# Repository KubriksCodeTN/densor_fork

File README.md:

# Densor

## About the project

Densor is an intraoral sensor platform, attached to regular dental retainers or aligners, that can take measurements inside the mouth. 

## Rationale

At present, in mouth measurements are typically made with external tools and in a controlled labaratory setting. Thus, real data from users daily lives is missing. To overcome this, we propose using widely used deltal retainers (or aligners), and enhance them with the Densor sensing platform. This way data is collected from inside the mouth without external tools. 

## Features

1. **Contactless transmission:** Densor is completely sealed and interacts with a smartphone via [NFC protocol](https://en.wikipedia.org/wiki/Near-field_communication). 
2. **Energy harvesting:** To stay powered Densor harvests energy, either from the [NFC communication itself](https://github.com/TUDSSL/densor/tree/master/NFC_harvester_battery_free) or from the [temperature gradient between the body and cold water](https://github.com/TUDSSL/densor/tree/master/TEG_harvester_battery_free). 
4. **Free of external hardware:** Operating Densor does not require any specialized tools, other than a NFC-compatible smartphone.

## Project layout

This repository contains the design (both hardware and software) of two versions of Densor, based on the source of energy harvesting. Each version of the project is contained in its own folder:

1. **[Densor with NFC-based energy harvesting from a smartphone](https://github.com/TUDSSL/densor/tree/master/NFC_harvester_battery_free)**, as presented in [this research article](https://dl.acm.org/doi/10.1145/3699746);
2. **[Densor with thermoelectric energy harvesting from drinking cold water](https://github.com/TUDSSL/densor/tree/master/TEG_harvester_battery_free)**.

## Copyright

Copyright (C) 2024 TU Delft Embedded Systems Group/[Sustainable Systems Laboratory](https://github.com/TUDSSL).

MIT License or otherwise specified. See [license](https://github.com/TUDSSL/densor/blob/master/LICENSE.txt) file for details.

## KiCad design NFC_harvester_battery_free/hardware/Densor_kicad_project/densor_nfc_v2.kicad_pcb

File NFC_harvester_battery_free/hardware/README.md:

# Densor - Hardware

## About the project 

This repository contains the design of Densor: an intraoral, actively powered, battery-free platform featuring multi-modal sensors and an extended lifespan. The repository consists of all components that make Densor:
- [Hardware](https://github.com/TUDSSL/densor/tree/master/NFC_harvester_battery_free/hardware)
- [Densor Firmware](https://github.com/TUDSSL/densor/tree/master/NFC_harvester_battery_free/software/DentalSensor_StorageProject)
- [Android app](https://github.com/TUDSSL/densor/tree/master/NFC_harvester_battery_free/software/source_ST25NFCApplication_V3_9)
- [Experiment setup and data collected](https://github.com/TUDSSL/densor/tree/master/NFC_harvester_battery_free/data/experiments)

This folder contains all the harware design files.

## Folder layout

- [Densor Kicad Project](https://github.com/TUDSSL/densor/tree/master/NFC_harvester_battery_free/hardware/Densor_kicad_project) contains the KiCad design files and can be opened with KiCad Version 8.
- [Datasheets](https://github.com/TUDSSL/densor/tree/master/NFC_harvester_battery_free/hardware/datasheets) contains the relavant datasheets of components used.
- [Gerbers Schematic](https://github.com/TUDSSL/densor/tree/master/NFC_harvester_battery_free/hardware/gerbers_schematic) contains the hardware output gerber files and schematic file in _.pdf_ format. This is useful if you wish to build Densor without any changes to the hardware.  

## List of components

| Component                  | Qty | Purchased from                                                                                                                                                                                                            |
|----------------------------|-----|---------------------------------------------------------------------------------------------------------------------------------------------------------------------------------------------------------------------------|
| Storage Capacitor          | 2   | [link to buy](https://www.digikey.com/en/products/detail/seiko-instruments/CPH3225A/8692444)                                                                                                                              |
| Decoupling Capacitor 100nF | 6   | [link to buy](https://nl.farnell.com/en-NL/kemet/c0603x104m4ractu/cap-mlcc-0-1uf-16v-0603/dp/2904941?st=0603%200.1uf)                                                                                                     |
| Zener Diode                | 1   | [link to buy](https://nl.farnell.com/on-semiconductor/mm3z3v6c/zener-diode-0-2w-3-6v-sod-323f/dp/2824925?CMP=i-ddd7-00001003)                                                                                             |
| Schottky Diode             | 1   | [link to buy](https://nl.farnell.com/nexperia/1ps76sb40-115/diode-schottky-sod323/dp/1349646?CMP=i-ddd7-00001003)                                                                                                         |
| Photo Diode                | 1   | [link to buy](https://nl.mouser.com/ProductDetail/Vishay-Semiconductors/VEMD1060X01?qs=pdQl6rENvLQkGyXPnNHd%2FQ%3D%3D&gclid=Cj0KCQjwmvSoBhDOARIsAK6aV7gSam9QYNxRe1G3dFcvfZGu4WvhXWOQdtZbTP3WNCzxGxyePn8TLa0aAiUbEALw_wcB) |
| Debug header               | 1   | [link to buy](https://nl.farnell.com/samtec/ftsh-105-01-l-d-k/connector-header-10pos-2row-1/dp/2856435?CMP=i-ddd7-00001003)                                                                                               |
| FPC connector              | 1   | [link to buy](https://nl.mouser.com/ProductDetail/Molex/503480-0800?qs=bodV9ulq6Gz33SKuZL445g%3D%3D&srsltid=AfmBOoqTYanmI1YXInVOzdpLIJ4tpVXYK3TQdvr3HJ4Y6jSj3ONDx022)                                                     |
| Pin Header 01x04           | 1   | [link to buy](https://nl.mouser.com/ProductDetail/Harwin/M20-9770446?qs=ulE8k0yEMYbCPpMPHeYh4w%3D%3D)                                                                                                                     |
| Resistor 100kohm           | 3   | [link to buy](https://nl.farnell.com/vishay/crcw0603100kfkea/res-100k-1-0-1w-0603-thick-film/dp/1469649?st=0603%20100k)                                                                                                   |
| Resistor 8Mohm             | 1   | [link to buy](https://nl.farnell.com/vishay/crcw06038m06fkea/res-8m06-1-0-1w-0603-thick-film/dp/2138717)                                                                                                                  |
| NFC Tag - ST25DV04K-JFR6D3 | 1   | [link to buy](https://www.digikey.nl/en/products/detail/stmicroelectronics/ST25DV64K-JFR6D3/7312974)                                                                                                                      |
| RTC - AM1805               | 1   | [link to buy](https://nl.farnell.com/en-NL/abracon/ab1805-t3/real-time-clock-i2c-qfn-16/dp/2467703?st=ab1805)                                                                                                             |
| MCU - STM32L021F3Ux        | 1   | [link to buy](https://www.digikey.nl/en/products/detail/stmicroelectronics/STM32L021F4U6TR/6166967)                                                                                                                       |
| Accelerometer - LIS2DW12   | 1   | [link to buy](https://nl.farnell.com/en-NL/stmicroelectronics/lis2dw12tr/lga-12-i-mems-digital-o-p-motion/dp/2849615?st=LIS2DW12TR)                                                                                       |
| SPDT - TS3A44159           | 1   | [link to buy](https://www.digikey.nl/en/products/detail/texas-instruments/TS3A44159RSVR/1909585)                                                                                                                          |
| Temperature sensor - TMP117AIDRVR | 1  | [link to buy](https://www.mouser.it/en/ProductDetail/Texas-Instruments/TMP117AIDRVR?qs=qSfuJ%252Bfl%2Fd6nh9h5HydMXQ%3D%3D) |
| Crystal                    | 1   | [link to buy](https://nl.farnell.com/en-NL/abracon/abs05w-32-768khz-j-2-t/crystal-32-768khz-4pf-smd-1-6/dp/2850126?st=abs05w)                                                                                             |
| Solder paste               | -   | [link to buy](https://www.digikey.nl/en/products/detail/chip-quik-inc/SMD291SNL50T3/5130160)                                                                                                                              |

## Copyright

Copyright (C) 2024 TU Delft Embedded Systems Group/Sustainable Systems Laboratory.

MIT Licence or otherwise specified. See [license](https://github.com/TUDSSL/ENGAGE/blob/master/LICENSE) file for details.

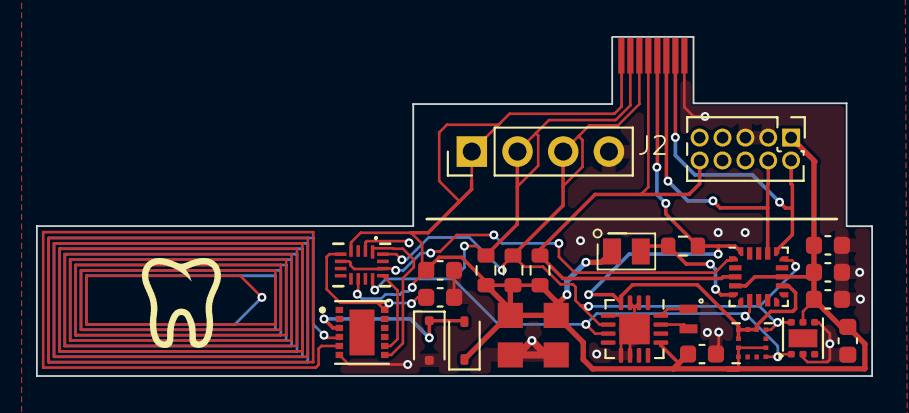
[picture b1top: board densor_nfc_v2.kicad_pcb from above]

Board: 2 copper layers, 46.4 x 18.8 mm, 26 parts (0 on the bottom side), 17 nets.

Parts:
C1, C2: C_Polarized; CPX3225A
C4, C5, C6, C7, C12, C13, C14: 100n; C_0603_1608Metric
D1: D_Zener_3v3; D_SOD-323F
D2: BAS316; D_SOD-323
D3: D_Photo; pd_vemd1060x01
J1: Conn_ARM_JTAG_SWD_10; PinHeader_2x05_P1.27mm_Vertical
J2: Conn_01x08_Pin; fpc_503480-0800
J3: Conn_01x04_Pin; PinHeader_1x04_P2.54mm_Vertical
R2, R3, R4: 100k; R_0603_1608Metric
R7: R; R_0603_1608Metric
U1: ST25DV04K-JFR6D3; PSON50P300X300X60-13N
U2: AM1805; QFN-16-1EP_3x3mm_P0.5mm_EP1.7x1.7mm
U3: TMP117xxDRV; WSON-6-1EP_2x2mm_P0.65mm_EP1x1.6mm
U4: STM32L011F3Ux; ST_UFQFPN-20_3x3mm_P0.5mm
U5: LIS2DW12; Kionix_LGA-12_2x2mm_P0.5mm_LayoutBorder2x4y
U6: TS3A44159; RSV16
Y1: Crystal; ABS05W_Crystal

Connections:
/AC0: U1.4 (AC0), U1.5 (AC1)
/NFC_SWITCH: U4.1 (PC14), U6.6 (IN3-4), U6.14 (IN1-2)
/PSW: J2.5, R7.2, U2.4 (PSW/nIRQ2), U4.12 (VSS), U4.20 (PB9), U5.5 (NC), U5.6 (GND), U5.7 (RES), U5.8 (GND)
/V_EH: D1.1 (K), D2.2 (A), U1.3 (V_EH)
/V_MCU: C1.1, C2.1, C4.1, C5.2, C6.1, C7.2, C12.2, C14.2, D2.1 (K), D3.1 (K), J1.1 (VTref), J2.1, J3.1, R2.1, R3.1, R4.1, U2.13 (VCC), U3.5 (V+), U4.4 (VDDA), U4.13 (VDD), U5.2 (CS), U5.9 (VDD), U5.10 (VDD_IO), U6.4 (COM3), U6.10 (VCC)
/V_NFC_switched: C13.2, U1.12 (VCC), U6.5 (NC3)
/i2c_scl: J2.2, J3.2, R2.2, U2.7 (SCL), U3.1 (SCL), U4.7 (PA4), U5.1 (SCL), U6.12 (COM1)
/i2c_scl_switched: U1.8 (SCL), U6.13 (NC1)
/i2c_sda: J2.3, J3.3, R3.2, U2.6 (SDA), U3.6 (SDA), U4.15 (PA10), U5.4 (SDA), U6.16 (COM2)
/i2c_sda_switched: U1.7 (SDA), U6.1 (NC2)
/nRST_MCU: J1.10 (~RESET), J2.4, R4.2, U4.3 (NRST)
/pd: D3.2 (A), R7.1, U4.5 (PA0)
/swclk: J1.4 (SWDCLK/TCK), J2.6, U4.17 (PA14)
/swdio: J1.2 (SWDIO/TMS), J2.7, U4.16 (PA13)
GND: C1.2, C2.2, C4.2, C5.1, C6.2, C7.1, C12.1, C13.1, C14.1, D1.2 (A), J1.3 (GND), J1.5 (GND), J2.8, J3.4, U1.6 (VSS), U2.2 (WDI), U2.3 (nEXTR), U2.5 (VBAT), U2.9 (VSS), U2.10 (EXTI), U2.17 (VSS), U3.2 (GND), U3.4 (ADD0), U6.2 (GND)
unnamed: U2.16 (XI), Y1.1
unnamed: U2.15 (XO), Y1.2

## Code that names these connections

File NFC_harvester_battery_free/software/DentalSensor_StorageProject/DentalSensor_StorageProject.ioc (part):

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Mcu.Name=STM32L021F4Ux
Mcu.Package=UFQFPN20
Mcu.UserName=STM32L021F4Ux
PA0-CK_IN.GPIOParameters=GPIO_Label
PA0-CK_IN.GPIO_Label=pd
PA0-CK_IN.Mode=IN0
PA0-CK_IN.Signal=ADC_IN0
PA1.GPIOParameters=GPIO_Label
PA1.GPIO_Label=moisture
PA1.Signal=ADC_IN1
PA10.GPIOParameters=GPIO_Pu
PA10.GPIO_Pu=GPIO_NOPULL
PA10.Mode=I2C
PA10.Signal=I2C1_SDA
PA13.Mode=Serial_Wire
PA13.Signal=SYS_SWDIO
PA14.Mode=Serial_Wire
PA14.Signal=SYS_SWCLK
PA4.GPIOParameters=GPIO_Pu
PA4.GPIO_Pu=GPIO_NOPULL
PA4.Mode=I2C
PA4.Signal=I2C1_SCL
PC14-OSC32_IN.GPIOParameters=PinState,GPIO_Label
PC14-OSC32_IN.GPIO_Label=NFC_SWITCH
PC14-OSC32_IN.PinState=GPIO_PIN_RESET
PC14-OSC32_IN.Signal=GPIO_Output
RCC.HSE_VALUE=8000000
RCC.SYSCLKFreq_VALUE=2097000
board=custom

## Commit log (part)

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2024-10-11 added license file
2024-10-11 added lifetime calculations
2024-11-26 Update README.md
    Stylistic changes to the main readme
2024-11-27 Update README.md
    Stylistic changes to the readme; addition of paper citation data
2024-11-27 Update README.md
    Small style edits to readme
2024-11-27 Update README.md
    Update license information
2024-11-27 Update LICENSE.txt
    Year change
2024-11-27 Update README.md
    Fix broken URL for license
2024-11-27 Update README.md
    fix typo
2024-11-27 Update README.md
    More text changes to readme
2024-11-27 Update README.md
    Further text edits.
2024-11-27 Update README.md
    Fix broken link to MIT license
2024-11-27 fix: upgrade gradle
    Upgrades gradle so the project can run on the latest versions of Android Studio.
2024-11-30 Update README.md
    LinkedIn profile of Jeffrey Pronk added
2024-12-01 added missing datasheets
